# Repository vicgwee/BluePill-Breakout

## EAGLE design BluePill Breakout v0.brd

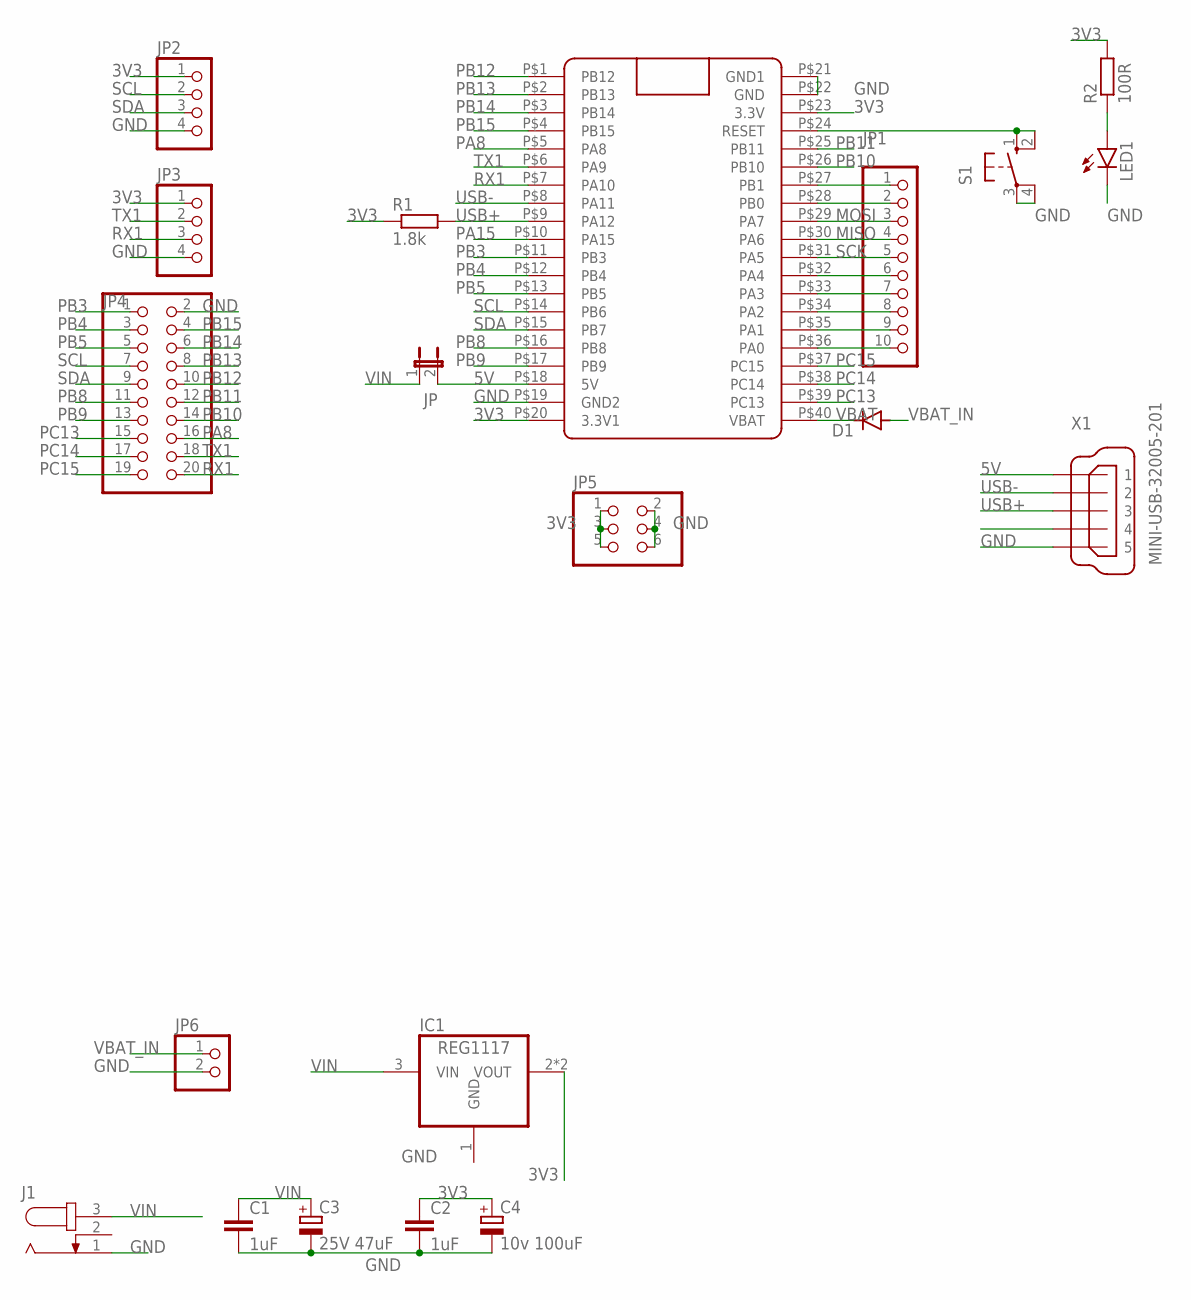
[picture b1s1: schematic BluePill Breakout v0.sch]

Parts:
C1, C2: 1uF; C0603
C3: 25V 47uF; E2,5-5
C4: 10v 100uF; E2,5-5
D1: DIODE-DO-214AC; DO-214AC
IC1: REG1117; SOT223
J1: JACK-PLUG0; SPC4077
JP: JP1E; JP1
JP1: PINHD-1X10; 1X10
JP2, JP3: PINHD-1X4; 1X04
JP4: PINHD-2X10; 2X10
JP5: PINHD-2X3; 2X03
JP6: PINHD-1X2; 1X02
LED1: LEDCHIPLED_0603; CHIPLED_0603
R1: 1.8k; R0603
R2: 100R; R0603
S1: 10-XX; B3F-10XX
U$1: BLUE_PILL
X1: MINI-USB-32005-201; 32005-201

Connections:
3V3: C2.1, C4.+, IC1.2 (VOUT), IC1.4 (VOUT), JP2.1, JP3.1, JP5.1, JP5.3, JP5.5, R1.1, R2.2, U$1.P$20 (3.3V1), U$1.P$23 (3.3V)
5V: JP.2, U$1.P$18 (5V), X1.1
GND: C1.2, C2.2, C3.-, C4.-, IC1.1 (GND), J1.1, JP2.4, JP3.4, JP4.2, JP5.2, JP5.4, JP5.6, JP6.2, LED1.C, S1.3, S1.4 (P1), U$1.P$19 (GND2), U$1.P$21 (GND1), U$1.P$22 (GND), X1.5
MISO: JP1.4, U$1.P$30 (PA6)
MOSI: JP1.3, U$1.P$29 (PA7)
unnamed: JP1.10, U$1.P$36 (PA0)
unnamed: JP1.9, U$1.P$35 (PA1)
unnamed: JP1.8, U$1.P$34 (PA2)
unnamed: JP1.7, U$1.P$33 (PA3)
unnamed: JP1.6, U$1.P$32 (PA4)
unnamed: S1.1 (S), S1.2 (S1), U$1.P$24 (RESET)
unnamed: LED1.A, R2.1
unnamed: JP1.1, U$1.P$27 (PB1)
unnamed: JP1.2, U$1.P$28 (PB0)
PA8: JP4.16, U$1.P$5 (PA8)
PA15: U$1.P$10 (PA15)
PB3: JP4.1, U$1.P$11 (PB3)
PB4: JP4.3, U$1.P$12 (PB4)
PB5: JP4.5, U$1.P$13 (PB5)
PB8: JP4.11, U$1.P$16 (PB8)
PB9: JP4.13, U$1.P$17 (PB9)
PB10: JP4.14, U$1.P$26 (PB10)
PB11: JP4.12, U$1.P$25 (PB11)
PB12: JP4.10, U$1.P$1 (PB12)
PB13: JP4.8, U$1.P$2 (PB13)
PB14: JP4.6, U$1.P$3 (PB14)
PB15: JP4.4, U$1.P$4 (PB15)
PC13: JP4.15, U$1.P$39 (PC13)
PC14: JP4.17, U$1.P$38 (PC14)
PC15: JP4.19, U$1.P$37 (PC15)
RX1: JP3.3, JP4.20, U$1.P$7 (PA10)
SCK: JP1.5, U$1.P$31 (PA5)
SCL: JP2.2, JP4.7, U$1.P$14 (PB6)
SDA: JP2.3, JP4.9, U$1.P$15 (PB7)
TX1: JP3.2, JP4.18, U$1.P$6 (PA9)
USB+: R1.2, U$1.P$9 (PA12), X1.3
USB-: U$1.P$8 (PA11), X1.2
VBAT: D1.C, U$1.P$40 (VBAT)
VBAT_IN: D1.A, JP6.1
VIN: C1.1, C3.+, IC1.3 (VIN), J1.3, JP.1

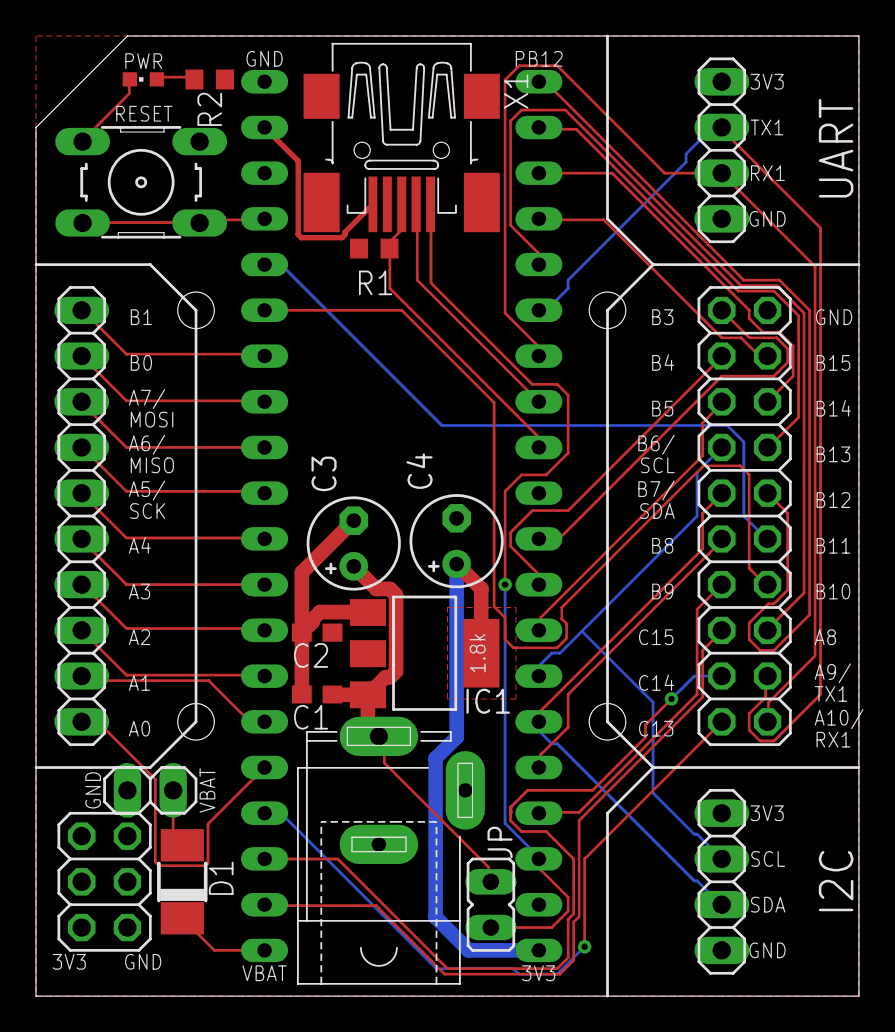
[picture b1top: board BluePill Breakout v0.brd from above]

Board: 2 copper layers, 45.7 x 53.3 mm, 20 parts (1 on the bottom side), 39 nets.

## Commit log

2019-10-15 Version 0
